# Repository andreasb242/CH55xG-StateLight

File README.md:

# CH55xG-StateLight
CH552 / CH551 USB State Light

## Source Code
Tab size is 4 Spaces

## PC Software
Basically working on Linux, no Messenger sync yet

## Protocol
This is the Target protocol, not 100% ready.

>Sended Text

>$ Received Text

All Texts are are terminated with \n, \r or Both (don't matter)

Normal Sequence:
>i

>$TODO

Check if Version is correct.

Set all LEDs:
>aRRGGBB

>$OK

RRGGBB is an RGB Hex Color
This will turn off blink.

Set single LED:
>sID RRGGBB

>$OK

ID is the LED ID, starting from 0, decimal
RRGGBB is an RGB Hex Color
This will turn off blink.

Set auto off time after XXX Seconds
>aXXX

>$OK

If there is no command received within XXX Seconds, turn off LEDs

Ping:
>p

>$OK

Used to prevent auto turn off

Blink:
>tXXX

>$OK

Set blink time to TTT * 100ms
Defaults to 5, => 500ms blink time.

>b255

>$OK

Blink all LEDs

>bID

>$OK

Blink LED ID, ID is decimal

Write config byte:
>caaa vvv

>$OK

aaa Address: decimal, 0 .. 127
vvv Value: decimal, 0 .. 255

Read config byte:
>raaa

>$OK vvv

aaa Address: decimal, 0 .. 127
vvv Value: decimal, 0 .. 255

Write value to EEPROM

## EEPROM Config
0 - 1: USB VID
2 - 3: USB PID
4: '>' if USB ID SHould be readed

5 - 23: Startup RGB Colors, RRGGBB.
24: '>' if RGB Colors should be read

25 ... n: Serial, Terminated with double 0, FF are ignored

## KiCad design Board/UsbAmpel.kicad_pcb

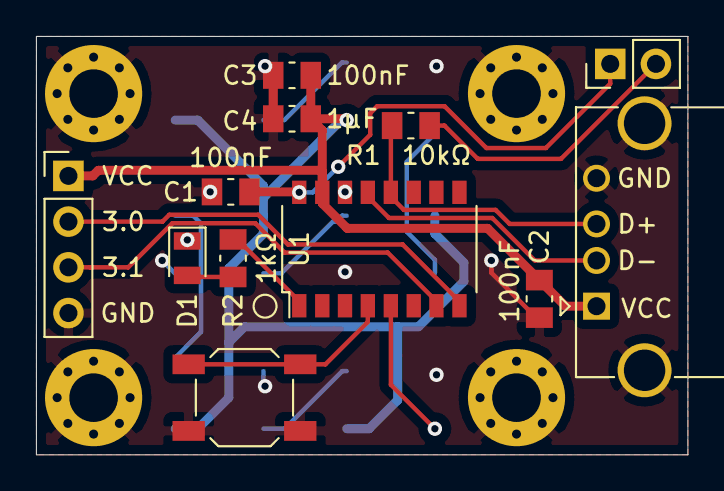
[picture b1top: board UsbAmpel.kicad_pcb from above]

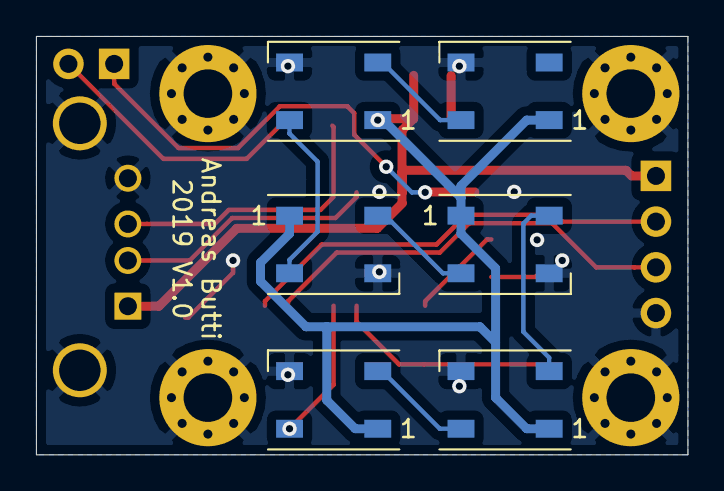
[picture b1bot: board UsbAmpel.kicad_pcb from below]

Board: 2 copper layers, 36.2 x 23.2 mm, 22 parts (6 on the bottom side), 17 nets.

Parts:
C1, C2, C3: 100nF; C_0805_2012Metric_Pad1.15x1.50mm_HandSolder
C4: 1µF; C_0805_2012Metric_Pad1.15x1.50mm_HandSolder
D1: LED; LED_0805_2012Metric_Pad0.97x1.50mm_HandSolder
D2, D3, D4, D5, D6, D7: WS2812B; LED_WS2812B_PLCC4_5.0x5.0mm_P3.2mm
J1: USB_A; USB_A_Horizontal
J2: Conn_01x02; PinHeader_1x02_P2.54mm_Vertical
J3: Conn_01x04; PinHeader_1x04_P2.54mm_Vertical
MK1, MK2, MK3, MK4: Mounting_Hole_PAD; MountingHole_2.7mm_M2.5_Pad_Via
R1: 10kΩ; R_0805_2012Metric_Pad1.15x1.50mm_HandSolder
R2: 1kΩ; R_0805_2012Metric_Pad1.15x1.50mm_HandSolder
SW1: SW_Push; SW_SPST_SKQG
U1: CH55xG; SOP-16_4.4x10.4mm_P1.27mm

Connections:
+3V3: C1.1, J2.1, U1.16
/BOOT: J2.2, R1.1
/D+: J1.3, R1.2, U1.12
/D-: J1.2, U1.13
/P1.6: SW1.1, U1.4
/P1.7: D2.4, U1.5
/P3.0: J3.2, U1.8
/P3.1: J3.3, U1.7
/P3.2: R2.2, U1.1
GND: C1.2, C2.2, C3.2, C4.2, D1.1, D2.3, D3.3, D4.3, D5.3, D6.3, D7.3, J1.4, J1.5, J3.4, MK1.1, MK2.1, MK3.1, MK4.1, SW1.2, U1.14
unnamed: D1.2, R2.1
unnamed: D2.2, D3.4
unnamed: D3.2, D4.4
unnamed: D4.2, D5.4
unnamed: D5.2, D6.4
unnamed: D6.2, D7.4
VCC: C2.1, C3.1, C4.1, D2.1, D3.1, D4.1, D5.1, D6.1, D7.1, J1.1, J3.1, U1.15

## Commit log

2019-04-29 Initial import
2019-04-29 Eclipse project
2019-04-30 Code cleanup
2019-04-30 Working on code cleanup - not compiling yet
2019-05-01 Try 2 firmware separation
2019-05-01 Test working
2019-05-01 USB to UART forwarding working (Test)
2019-05-01 Removed I2C
2019-05-01 WS2812B also working
2019-05-01 LEDs on the correct pin
2019-05-01 LED Control working over USB
2019-05-01 Firmware more or less working
2019-05-03 Cleanup - removed example code
2019-05-03 Code Documentation / Cleanup
2019-05-03 Readme update
2019-05-03 Moved USB Stuff to separate file
2019-05-03 Descriptor cleanup
2019-05-04 USB Code Cleanup
2019-05-04 Cleanup / USB IDs
2019-05-04 Last fixes - current date as serial number
2019-05-04 Python App for Ubuntu - first try
2019-05-04 Icon update working
2019-05-04 Ubuntu menu working
2019-05-04 Config
2019-05-10 Blink working, EEPROM Working, Protocol improved and documented
2019-05-10 EEProm
    -Small fixed
    -Reading / Writing Eeprom scripts
2019-05-10 Documentation / Code cleanup
2019-05-10 Loading VID / PID from EEPROM working
2019-05-10 Base / Sampel EEPROM Image
2019-05-10 Load predefined colors from EEPROM
2019-05-11 Read Serial from EEPROM, firmware finished
2019-05-11 Windows Readme
2019-05-11 Windwos Application
2019-05-11 Setting Color to device is working
2019-05-11 Cleanup
2019-05-11 Load config from app.config
2019-05-11 Error handling
2019-05-11 Connection test
2019-05-11 Timeout handling
2019-05-12 Fix Timeout handling - Checkin Firmware
2019-05-12 Send multiple colors
2019-05-12 Blink fix
2019-05-12 Timer working
2019-05-12 App Configuration
2019-05-13 Plugin interface to implement different messenger types
2019-05-13 Fixed Open Port bug / Plugin Interface
2019-05-15 Linux - Pidgin Sync working
2019-05-21 Connecting Lync2010 working
2019-05-22 Lync plugin working
2019-05-25 Plugin state mapping
2019-05-25 Working
2019-05-26 Documentation
2019-05-27 Asynchrone command execution
2019-05-27 Serial handling
2019-05-27 Add timeout for write, fix random issues
2019-05-30 Plugin Loading, checking for for multiple instances
2019-05-30 Auto connect lync if not started on startup
2019-05-30 If the device is reconnected, send color again
2019-05-30 Detect calling
2019-06-03 Setup Script
2019-06-03 Fixed plugin loader
2019-06-03 Mapping
2019-06-03 Plugin Loading
2019-06-21 Handle turn off LEDs on USB Standby
2019-06-22 Exception Handling
2019-06-22 Lync2013 working, if the SDK DLLs are copied, some loading issue
2019-06-22 Lync 2013 working
2019-06-22 Release script
2019-07-07 Submodule
